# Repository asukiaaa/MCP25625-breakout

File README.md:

# MCP25625-breakout

A breakout board of MCP25625.

Schematic: [docs/mcp25625-breakout.pdf](docs/mcp25625-breakout.pdf)

## Components

- MCP25625 SSOP28
- 0.1uf 0402
- 22pf 0402
- 120 ohm 0402
- [slide switch smd](https://akizukidenshi.com/catalog/g/gP-13989/)
- [16MHz crystal](https://akizukidenshi.com/catalog/g/gP-02457/)

## Where to buy

[MCP25625-breakout](https://www.switch-science.com/catalog/7228/)

## License

MIT

## References

- [CanBusMCP2515-arduino](https://github.com/asukiaaa/CanBusMCP2515-arduino)
- [CANをArduinoで使ってみた](https://asukiaaa.blogspot.com/2021/07/canarduino.html)
- [製品紹介 MCP25625-breakout](https://asukiaaa.blogspot.com/2021/06/mcp25625-breakout.html)

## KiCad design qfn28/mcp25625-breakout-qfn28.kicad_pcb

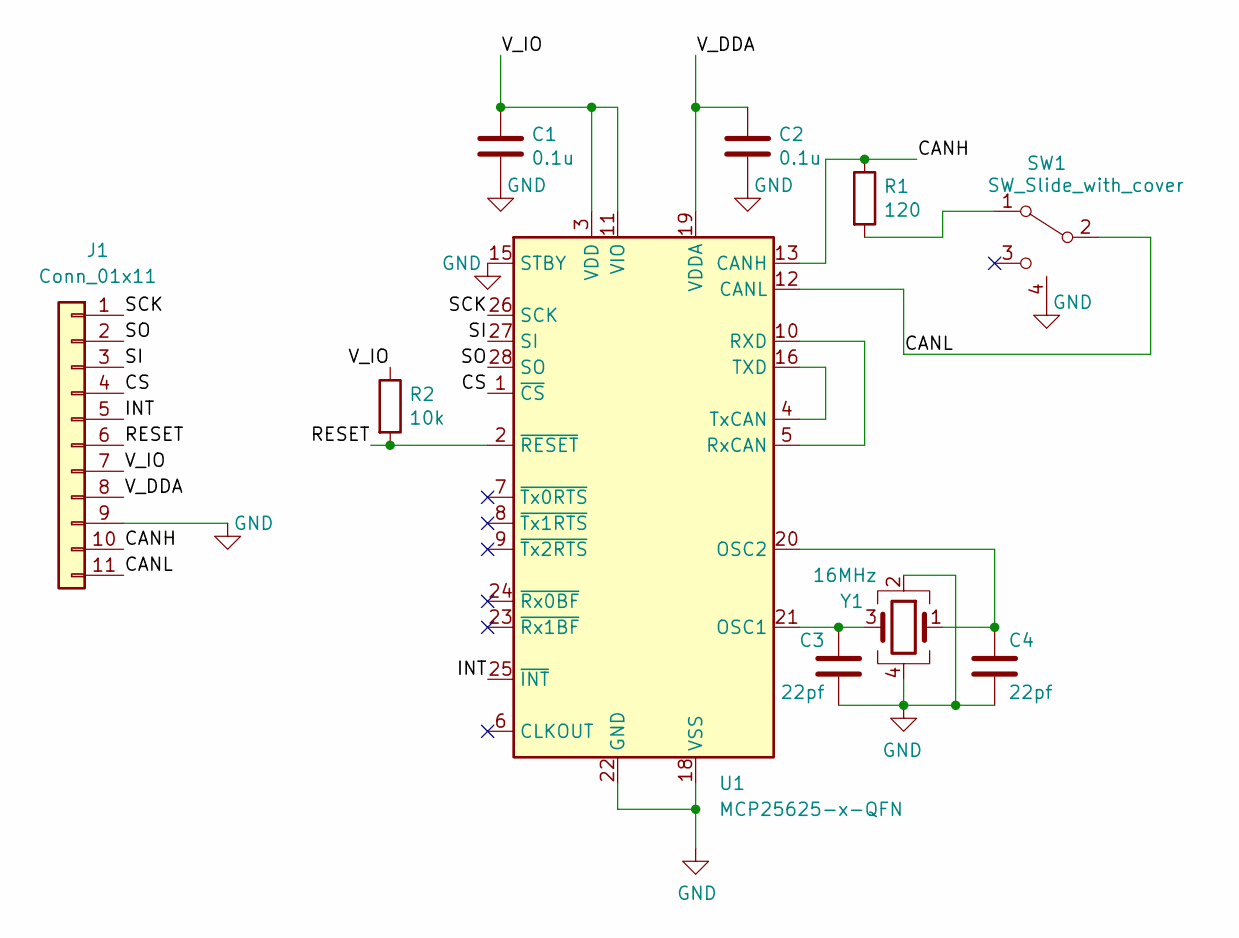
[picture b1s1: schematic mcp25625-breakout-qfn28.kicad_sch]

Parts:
C1, C2: 0.1u; C_0402_1005Metric
C3, C4: 22pf; C_0402_1005Metric
J1: Conn_01x11; PinHeader_1x11_P2.54mm_Vertical_witout_silk
R1: 120; R_0402_1005Metric
R2: 10k; R_0201_0603Metric
SW1: SW_Slide_with_cover; slide_switch_smd
U1: MCP25625-x-QFN; QFN-28-1EP_6x6mm_P0.65mm_EP4.25x4.25mm
Y1: 16MHz; Crystal_SMD_SeikoEpson_FA238-4Pin_3.2x2.5mm

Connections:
/CANH: J1.10, R1.1, U1.13 (CANH)
/CANL: J1.11, SW1.2 (B), U1.12 (CANL)
/CS: J1.4, U1.1 (~CS)
/INT: J1.5, U1.25 (~INT)
/RESET: J1.6, R2.2, U1.2 (~RESET)
/SCK: J1.1, U1.26 (SCK)
/SI: J1.3, U1.27 (SI)
/SO: J1.2, U1.28 (SO)
/V_DDA: C2.1, J1.8, U1.19 (VDDA)
/V_IO: C1.1, J1.7, R2.1, U1.3 (VDD), U1.11 (VIO)
GND: C1.2, C2.2, C3.2, C4.2, J1.9, SW1.4 (Cover), U1.15 (STBY), U1.18 (VSS), U1.22 (GND), Y1.2, Y1.4
unnamed: R1.2, SW1.1 (A)
unnamed: C3.1, U1.21 (OSC1), Y1.3
unnamed: C4.1, U1.20 (OSC2), Y1.1
unnamed: U1.5 (RxCAN), U1.10 (RXD)
unnamed: U1.4 (TxCAN), U1.16 (TXD)

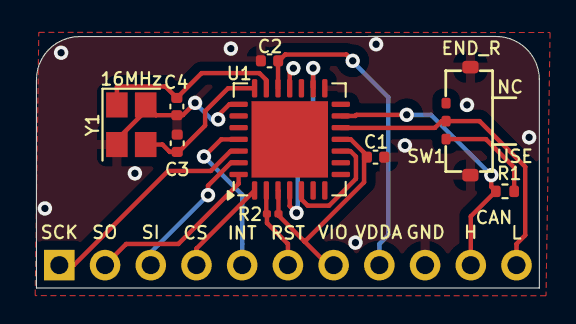
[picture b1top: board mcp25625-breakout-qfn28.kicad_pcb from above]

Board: 2 copper layers, 27.9 x 14.0 mm, 10 parts (0 on the bottom side), 16 nets.

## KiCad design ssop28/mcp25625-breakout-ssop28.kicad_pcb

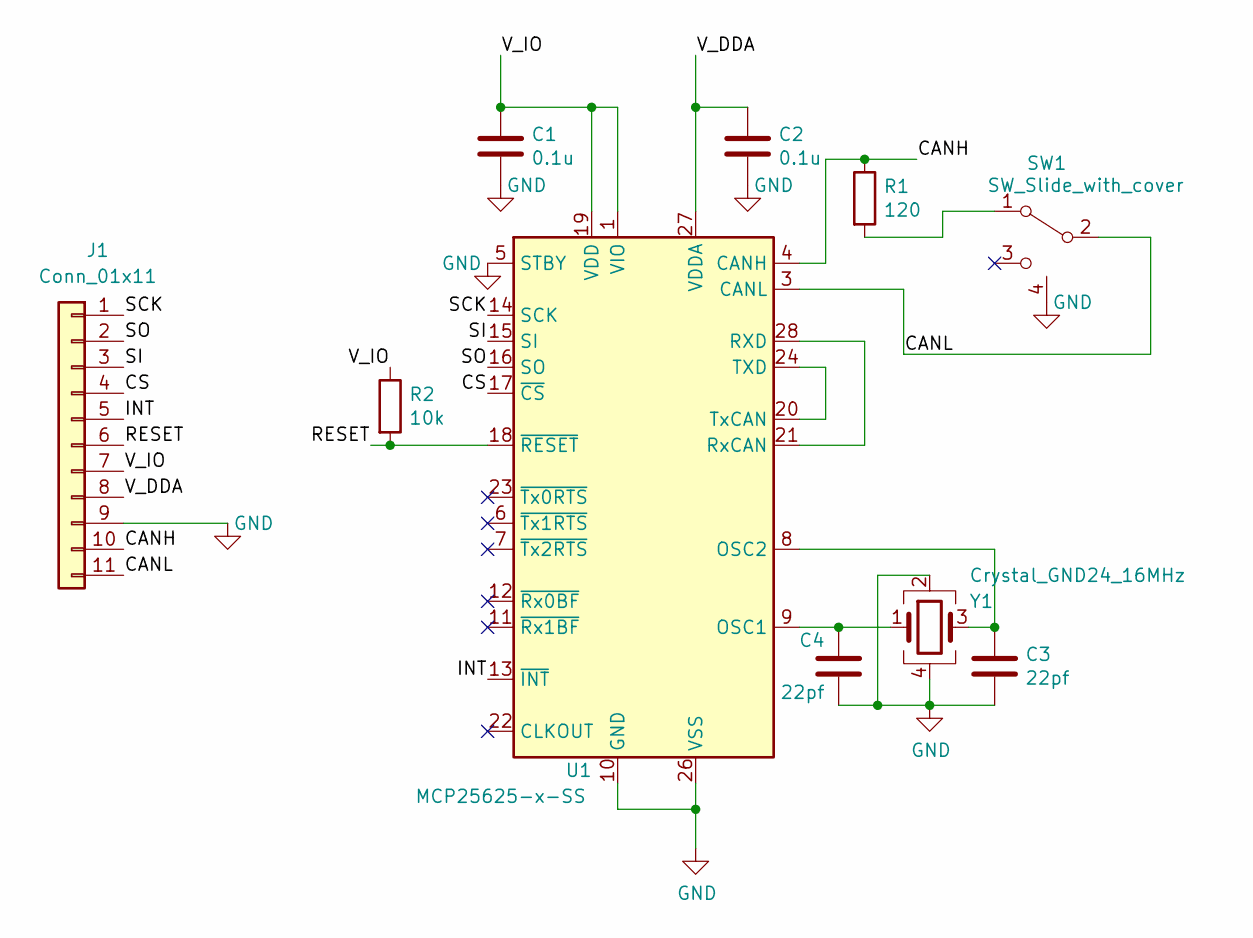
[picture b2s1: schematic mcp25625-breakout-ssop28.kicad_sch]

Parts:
C1, C2: 0.1u; C_0402_1005Metric
C3, C4: 22pf; C_0402_1005Metric
J1: Conn_01x11; PinHeader_1x11_P2.54mm_Vertical_witout_silk
R1: 120; R_0402_1005Metric
R2: 10k; R_0402_1005Metric
SW1: SW_Slide_with_cover; slide_switch_smd
U1: MCP25625-x-SS; SSOP-28_5.3x10.2mm_P0.65mm
Y1: Crystal_GND24_16MHz; Crystal_SMD_SeikoEpson_FA238-4Pin_3.2x2.5mm

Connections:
/CANH: J1.10, R1.1, U1.4 (CANH)
/CANL: J1.11, SW1.2 (B), U1.3 (CANL)
/CS: J1.4, U1.17 (~CS)
/INT: J1.5, U1.13 (~INT)
/RESET: J1.6, R2.2, U1.18 (~RESET)
/SCK: J1.1, U1.14 (SCK)
/SI: J1.3, U1.15 (SI)
/SO: J1.2, U1.16 (SO)
/V_DDA: C2.1, J1.8, U1.27 (VDDA)
/V_IO: C1.1, J1.7, R2.1, U1.1 (VIO), U1.19 (VDD)
GND: C1.2, C2.2, C3.2, C4.2, J1.9, SW1.4 (Cover), U1.5 (STBY), U1.10 (GND), U1.26 (VSS), Y1.2, Y1.4
unnamed: C3.1, U1.8 (OSC2), Y1.3
unnamed: C4.1, U1.9 (OSC1), Y1.1
unnamed: R1.2, SW1.1 (A)
unnamed: U1.20 (TxCAN), U1.24 (TXD)
unnamed: U1.21 (RxCAN), U1.28 (RXD)

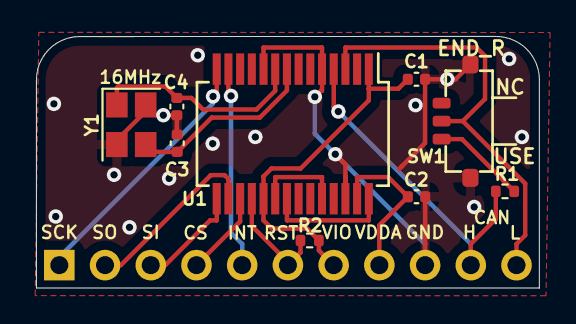
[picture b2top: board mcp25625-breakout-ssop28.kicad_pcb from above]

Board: 2 copper layers, 27.9 x 14.0 mm, 10 parts (0 on the bottom side), 16 nets.

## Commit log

2021-06-06 Initial commit as Rev2021.06
2021-06-08 Fill again
2021-06-08 Remove -bak files from git
2021-06-20 Add bom and image in docs directory
2021-06-20 Show image and shop link to readme
2021-06-22 Add pdf of schematic
2021-07-11 Add reset pad and 16MHz mems as rev2021.07
2021-10-08 Replace rezonator to crystal
2021-10-08 Add reference links
2022-05-01 Apply KiCad6
2022-05-01 Apply KiCad6 lib
2023-02-01 Change to not hand solder pad for crystal
2023-04-17 Add resistor between rst and vio as rev2023.05
2024-04-12 Put current project to ssop28 dir
2024-04-12 Rename project in ssop28 dir
2024-04-12 Add qfn28 project as rev2024.05
2024-05-28 Update bom for qfn package
2024-05-28 Show 16MHz silk on pcb for qfn
